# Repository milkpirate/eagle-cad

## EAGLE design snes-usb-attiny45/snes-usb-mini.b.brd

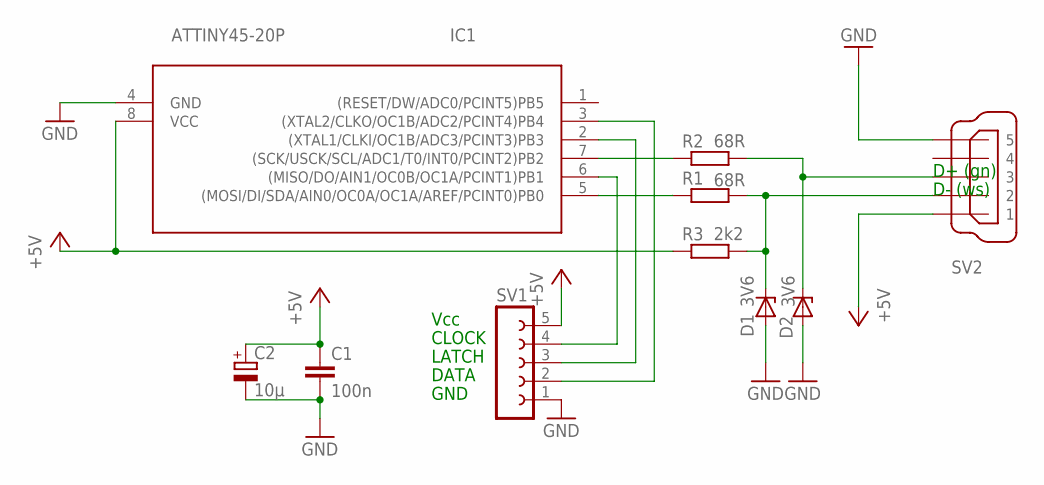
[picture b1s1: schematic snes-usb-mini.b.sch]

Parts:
C1: 100n; C025-024X044
C2: 10µ; E2-4
D1, D2: 3V6; ZDIO-2.5
IC1: ATTINY45-20P; DIL08
R1: 68R; 0207/10
R2: 68R; 0411V
R3: 2k2; 0204V
SV1: FE05-1
SV2: MINI-USB_SHIELD5P2-32005-601; 32005-601

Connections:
+5V: C1.1, C2.+, IC1.8 (VCC), R3.1, SV1.5, SV2.1
GND: C1.2, C2.-, D1.A, D2.A, IC1.4 (GND), SV1.1, SV2.5
unnamed: IC1.5 ((MOSI/DI/SDA/AIN0/OC0A/OC1A/AREF/PCINT0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), R1.1
unnamed: IC1.7 ((SCK/USCK/SCL/ADC1/T0/INT0/PCINT2)PB2), R2.1
unnamed: D1.C, R1.2, R3.2, SV2.2
unnamed: D2.C, R2.2, SV2.3
unnamed: IC1.6 ((MISO/DO/AIN1/OC0B/OC1A/PCINT1)PB1), SV1.4
unnamed: IC1.2 ((XTAL1/CLKI/OC1B/ADC3/PCINT3)PB3), SV1.3
unnamed: IC1.3 ((XTAL2/CLKO/OC1B/ADC2/PCINT4)PB4), SV1.2

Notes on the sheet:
GND
DATA
LATCH
CLOCK
Vcc
D- (ws)
D+ (gn)

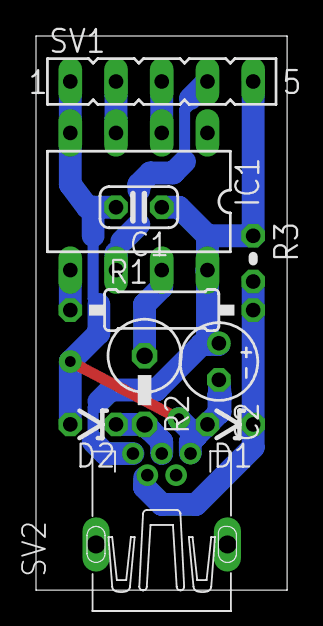
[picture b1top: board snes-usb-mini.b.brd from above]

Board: 2 copper layers, 14.0 x 30.8 mm, 10 parts (0 on the bottom side), 9 nets.

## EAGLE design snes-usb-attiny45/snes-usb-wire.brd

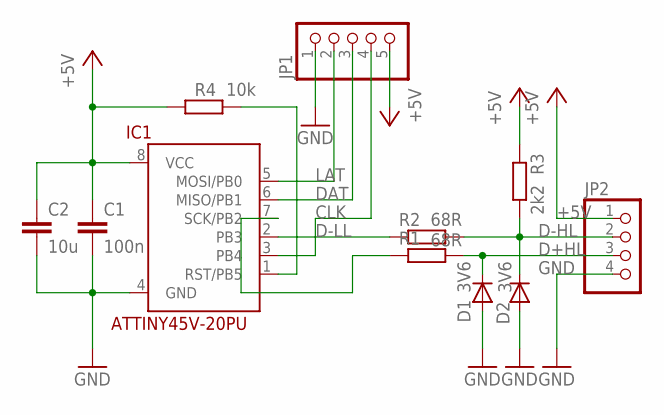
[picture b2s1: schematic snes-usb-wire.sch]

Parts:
C1: 100n; C0805K
C2: 10u; C0805K
D1, D2: 3V6; D-2.5
IC1: ATTINY45V-20PU; DIL08
JP1: PINHD-1X5; 1X05
JP2: PINHD-1X4; 1X04
R1, R2: 68R; M0805
R3: 2k2; M0805
R4: 10k; M0805

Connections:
+5V: C1.1, C2.1, IC1.8 (VCC), JP1.5, JP2.1, R3.1, R4.1
CLK: IC1.3 (PB4), JP1.4
D+HL: D1.C, JP2.3, R1.2
D-HL: D2.C, JP2.2, R2.2, R3.2
D-LL: IC1.2 (PB3), R2.1
DAT: IC1.6 (MISO/PB1), JP1.3
GND: C1.2, C2.2, D1.A, D2.A, IC1.4 (GND), JP1.1, JP2.4
LAT: IC1.5 (MOSI/PB0), JP1.2
unnamed: IC1.1 (RST/PB5), R4.2
unnamed: IC1.7 (SCK/PB2), R1.1

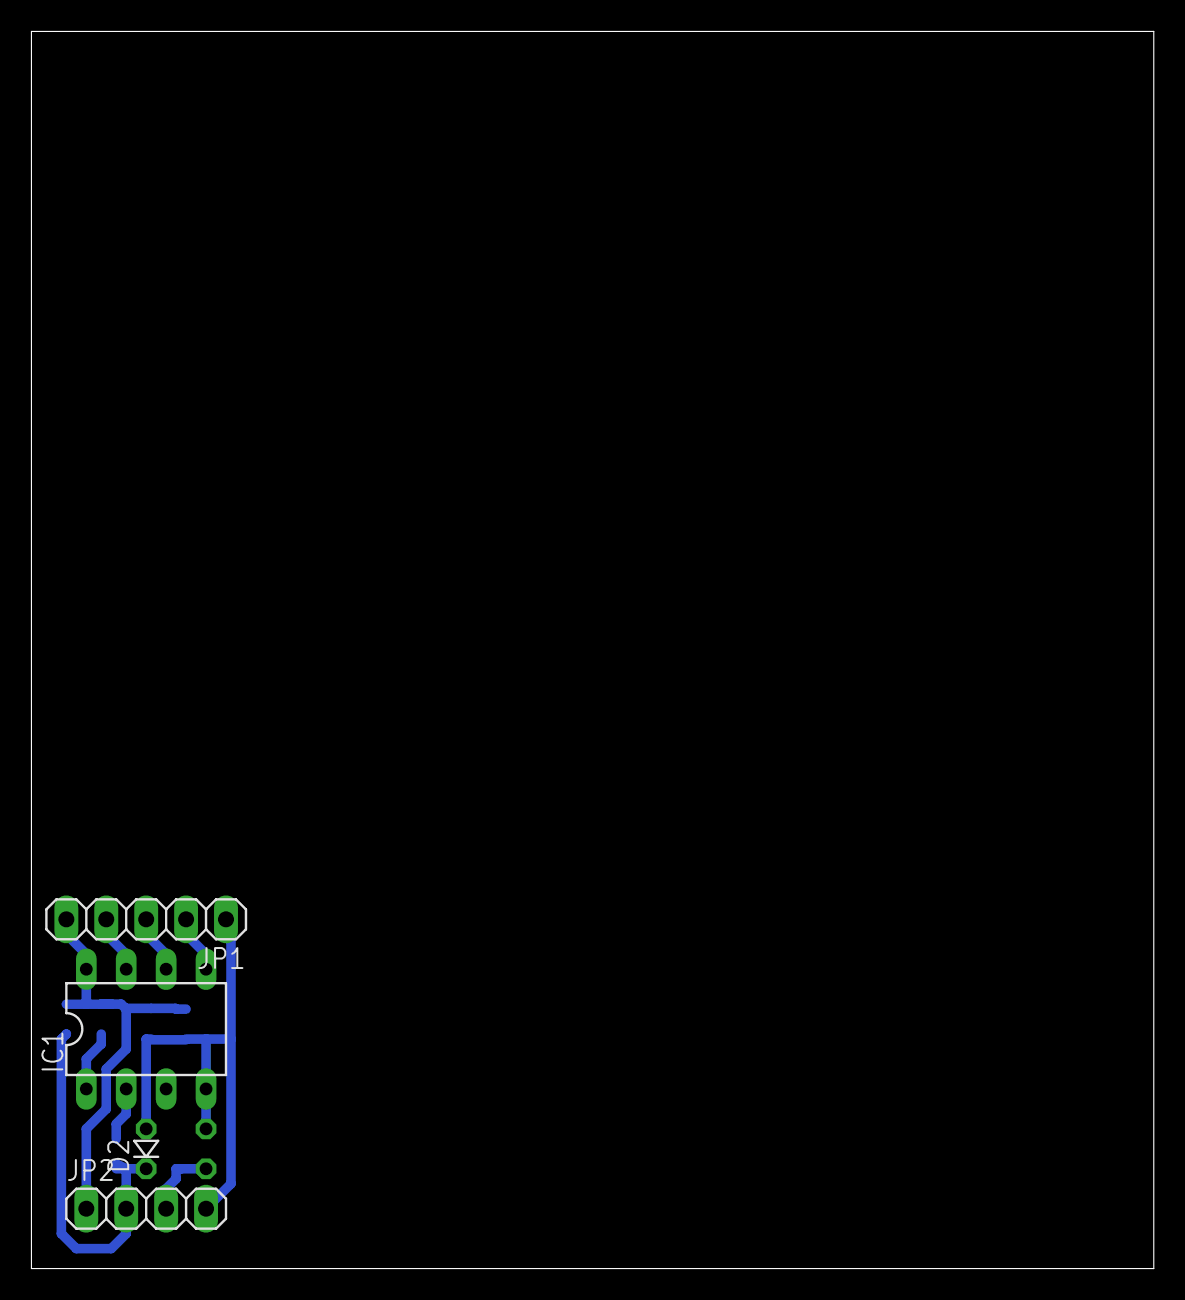
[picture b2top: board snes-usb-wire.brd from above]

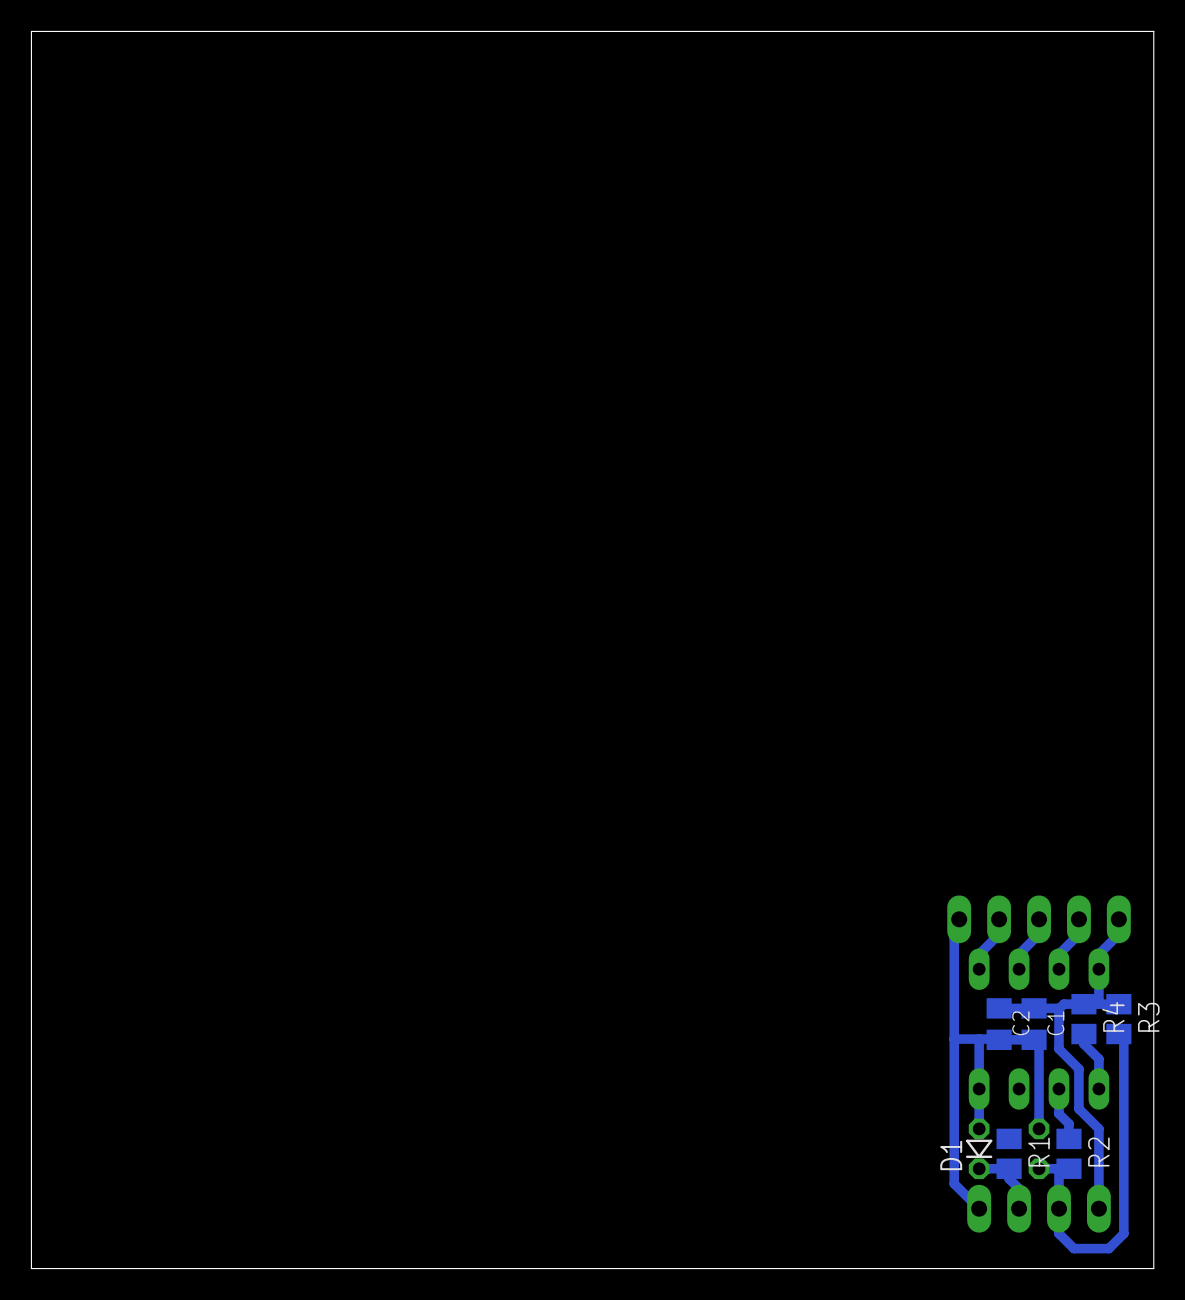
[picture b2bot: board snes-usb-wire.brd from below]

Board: 2 copper layers, 71.4 x 78.7 mm, 11 parts (7 on the bottom side), 10 nets.

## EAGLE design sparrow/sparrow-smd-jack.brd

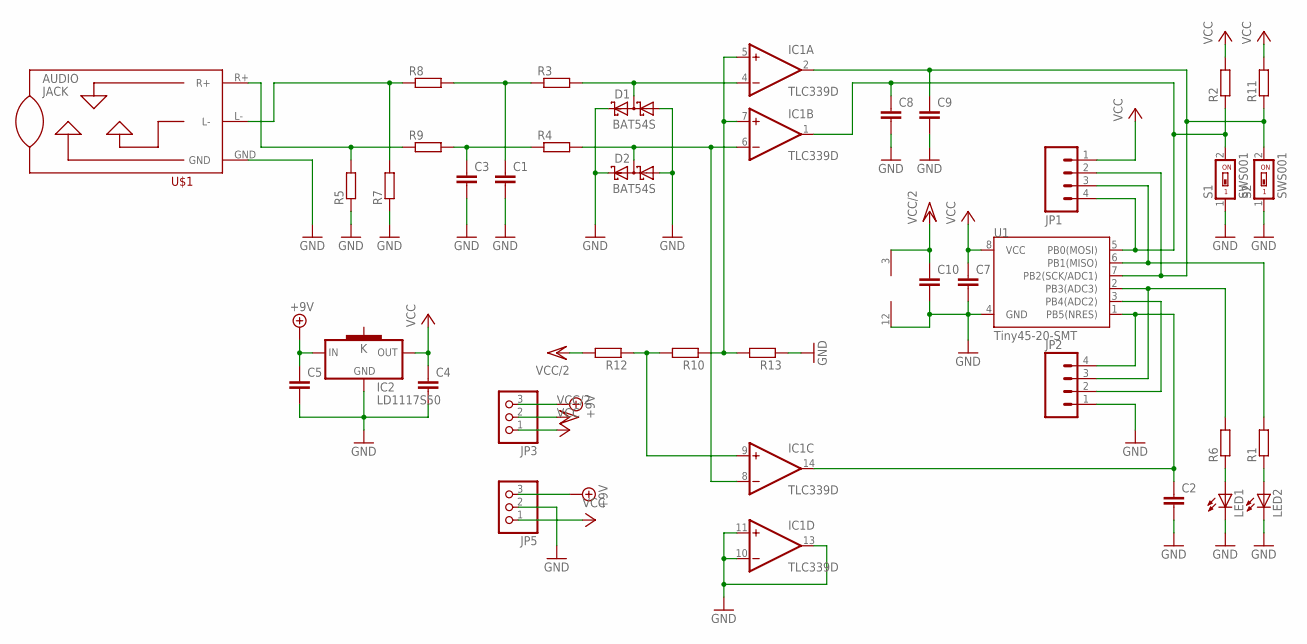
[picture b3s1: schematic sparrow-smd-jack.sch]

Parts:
C1, C2, C3, C4, C5, C7, C8, C9, C10: C-EUC0805K; C0805K
D1, D2: BAT54S; SOT23
IC1: TLC339D; SO14
IC2: LD1117S50; SOT223
JP1, JP2: M04PTH; 1X04
JP3, JP5: PINHD-1X3; 1X03
LED1, LED2: LEDCHIP-LED0805; CHIP-LED0805
R1, R2, R3, R4, R5, R6, R7, R8, R9, R10, R11, R12, R13: R-EU_M0805; M0805
S1, S2: SWS001; SMS-001
U1: Tiny45-20-SMT; SO08-EIAJ
U$1: AUDIO-JACK-SMDSMD; AUDIO-JACK-SMD

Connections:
+9V: C5.1, IC2.3 (IN), JP3.3, JP5.3
GND: C1.2, C2.2, C3.2, C4.2, C5.2, C7.2, C8.2, C9.2, C10.2, D1.1 (A1), D1.2 (C2), D2.1 (A1), D2.2 (C2), IC1.10 (-IN), IC1.11 (+IN), IC1.12 (V-), IC1.13 (OUT), IC2.1 (GND), JP2.1, JP5.2, LED1.C, LED2.C, R5.1, R7.1, R13.1, S1.1, S2.1, U1.4 (GND), U$1.GND
unnamed: D1.3 (C1A2), IC1.4 (-IN), R3.2
unnamed: JP2.3, R6.2, U1.2 (PB3(ADC3))
unnamed: C2.1, IC1.14 (OUT), JP2.4, U1.1 (PB5(NRES))
unnamed: JP2.2, U1.3 (PB4(ADC2))
unnamed: D2.3 (C1A2), IC1.6 (-IN), IC1.8 (-IN), R4.2
unnamed: JP1.3, R1.2, U1.6 (PB1(MISO))
unnamed: C9.1, IC1.2 (OUT), JP1.2, R11.1, S2.2, U1.7 (PB2(SCK/ADC1))
unnamed: C1.1, R3.1, R8.2
unnamed: LED1.A, R6.1
unnamed: LED2.A, R1.1
unnamed: C3.1, R4.1, R9.2
unnamed: C8.1, IC1.1 (OUT), JP1.4, R2.1, S1.2, U1.5 (PB0(MOSI))
unnamed: R7.2, R8.1, U$1.L-
unnamed: R5.2, R9.1, U$1.R+
unnamed: IC1.9 (+IN), R10.2, R12.1
unnamed: IC1.5 (+IN), IC1.7 (+IN), R10.1, R13.2
VCC: C4.1, C7.1, IC2.2 (OUT), JP1.1, JP3.1, JP5.1, R2.2, R11.2, U1.8 (VCC)
VCC/2: C10.1, IC1.3 (V+), JP3.2, R12.2

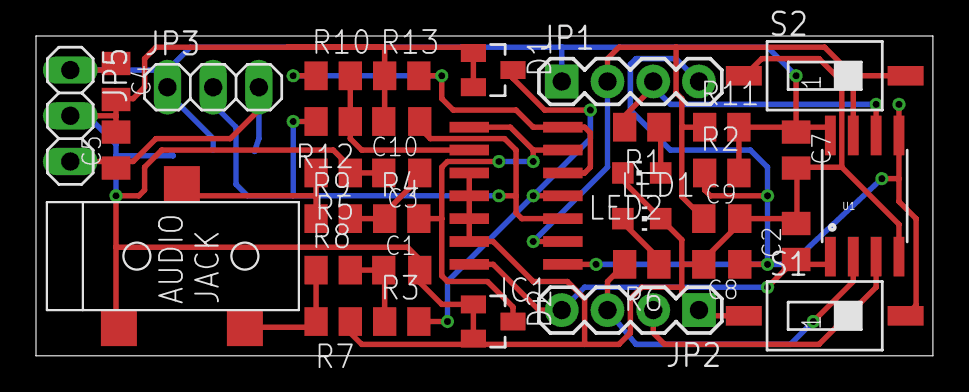
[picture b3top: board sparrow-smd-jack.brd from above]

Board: 2 copper layers, 49.8 x 17.8 mm, 36 parts (1 on the bottom side), 20 nets.

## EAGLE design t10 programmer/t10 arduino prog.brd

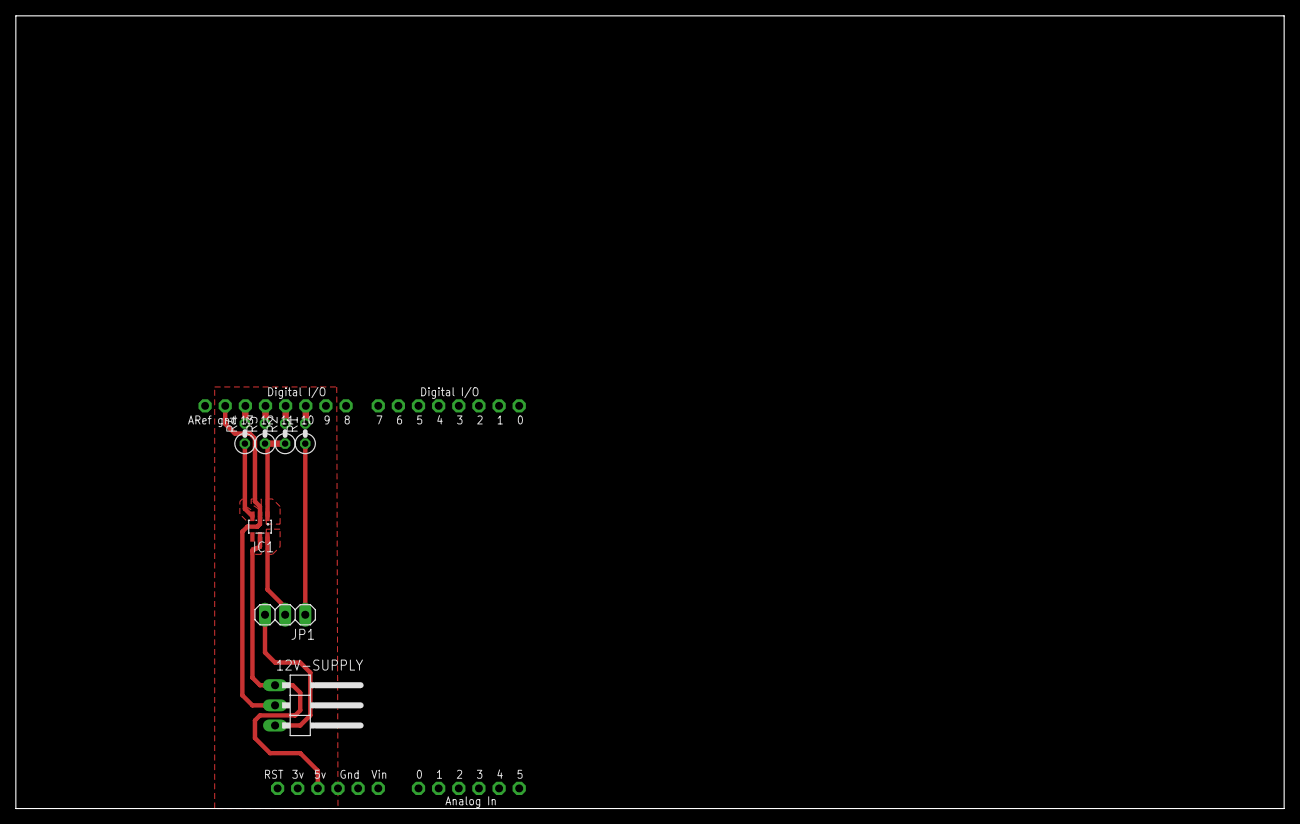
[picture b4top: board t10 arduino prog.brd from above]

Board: 2 copper layers, 160.0 x 100.0 mm, 8 parts (0 on the bottom side), 11 nets.

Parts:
12V-SUPPLY: 1X03/90
IC1: ATTINY10; SOT23-6
JP1: 1X03
R1, R2, R3, R4: 2k2; 0207/2V
U$1: ARDUINO-NOHOLE

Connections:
+5V: 12V-SUPPLY.1, IC1.5, U$1.5V
+12V: 12V-SUPPLY.3, JP1.3
GND: 12V-SUPPLY.2, IC1.2, U$1.GND, U$1.GND1, U$1.GND2
unnamed: R1.2, U$1.D10
unnamed: R2.2, U$1.D11
unnamed: R3.2, U$1.D12
unnamed: R4.2, U$1.D13
unnamed: IC1.1, R2.1, R3.1
unnamed: IC1.3, R4.1
unnamed: JP1.1, R1.1
unnamed: IC1.6, JP1.2

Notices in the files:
parts and their libraries:
SparkFun-DigitalIC: Licensing: Creative Commons ShareAlike 4.0 International - https://creativecommons.org/licenses/by-sa/4.0
